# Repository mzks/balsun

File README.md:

# balsun - Balloon adaptive link board with Wi-SUN

This is an arduino-compatible board for balloon experiments.

## Features

 - Arduino UNO R4 Minima-compatible hardware
 - Low EMC noise for general balloon RF system
 - Wi-SUN FAN communication (MIC/TELEC, FCC)
 - Open hardware and software

## Specifications

 - MCU Renesas RA4M1
 - 5V IOs (GPIO, UART, SCI, I2C, CAN, ADC, DAC, OpAmp) with castellated holes
 - Write bootloader/sketch/program via USB type-C
 - Multi power sources (1.5--5V) and more (users can mount their regurator via through holes)
 - PCB size is 64.5 * 53.4 mm, FR-4 1.6 mm
 - Wi-SUN with BP35C5 (RoHM) and two types of the anntena

## How can I get?

All hardware design is published as KiCAD files.
You can ask some manifactures to build them.
If you are customer of JLCPCB, Elecrow, FusionPCB, or PCBWay, you can find the zip files including everything to build PCB in [here](/hardware/info/gerber_to_order).
For PCBA, BOM and Pos files are [here](/hardware/info).
All parts are available in Mouser (2024 Oct. 24).

## Contact
Keita Mizukoshi (mizukoshi.keita@jaxa.jp)

## Local information
Japanese specific information and discussion among local balloon community in [jp-docs](/docs/jp-docs.md).

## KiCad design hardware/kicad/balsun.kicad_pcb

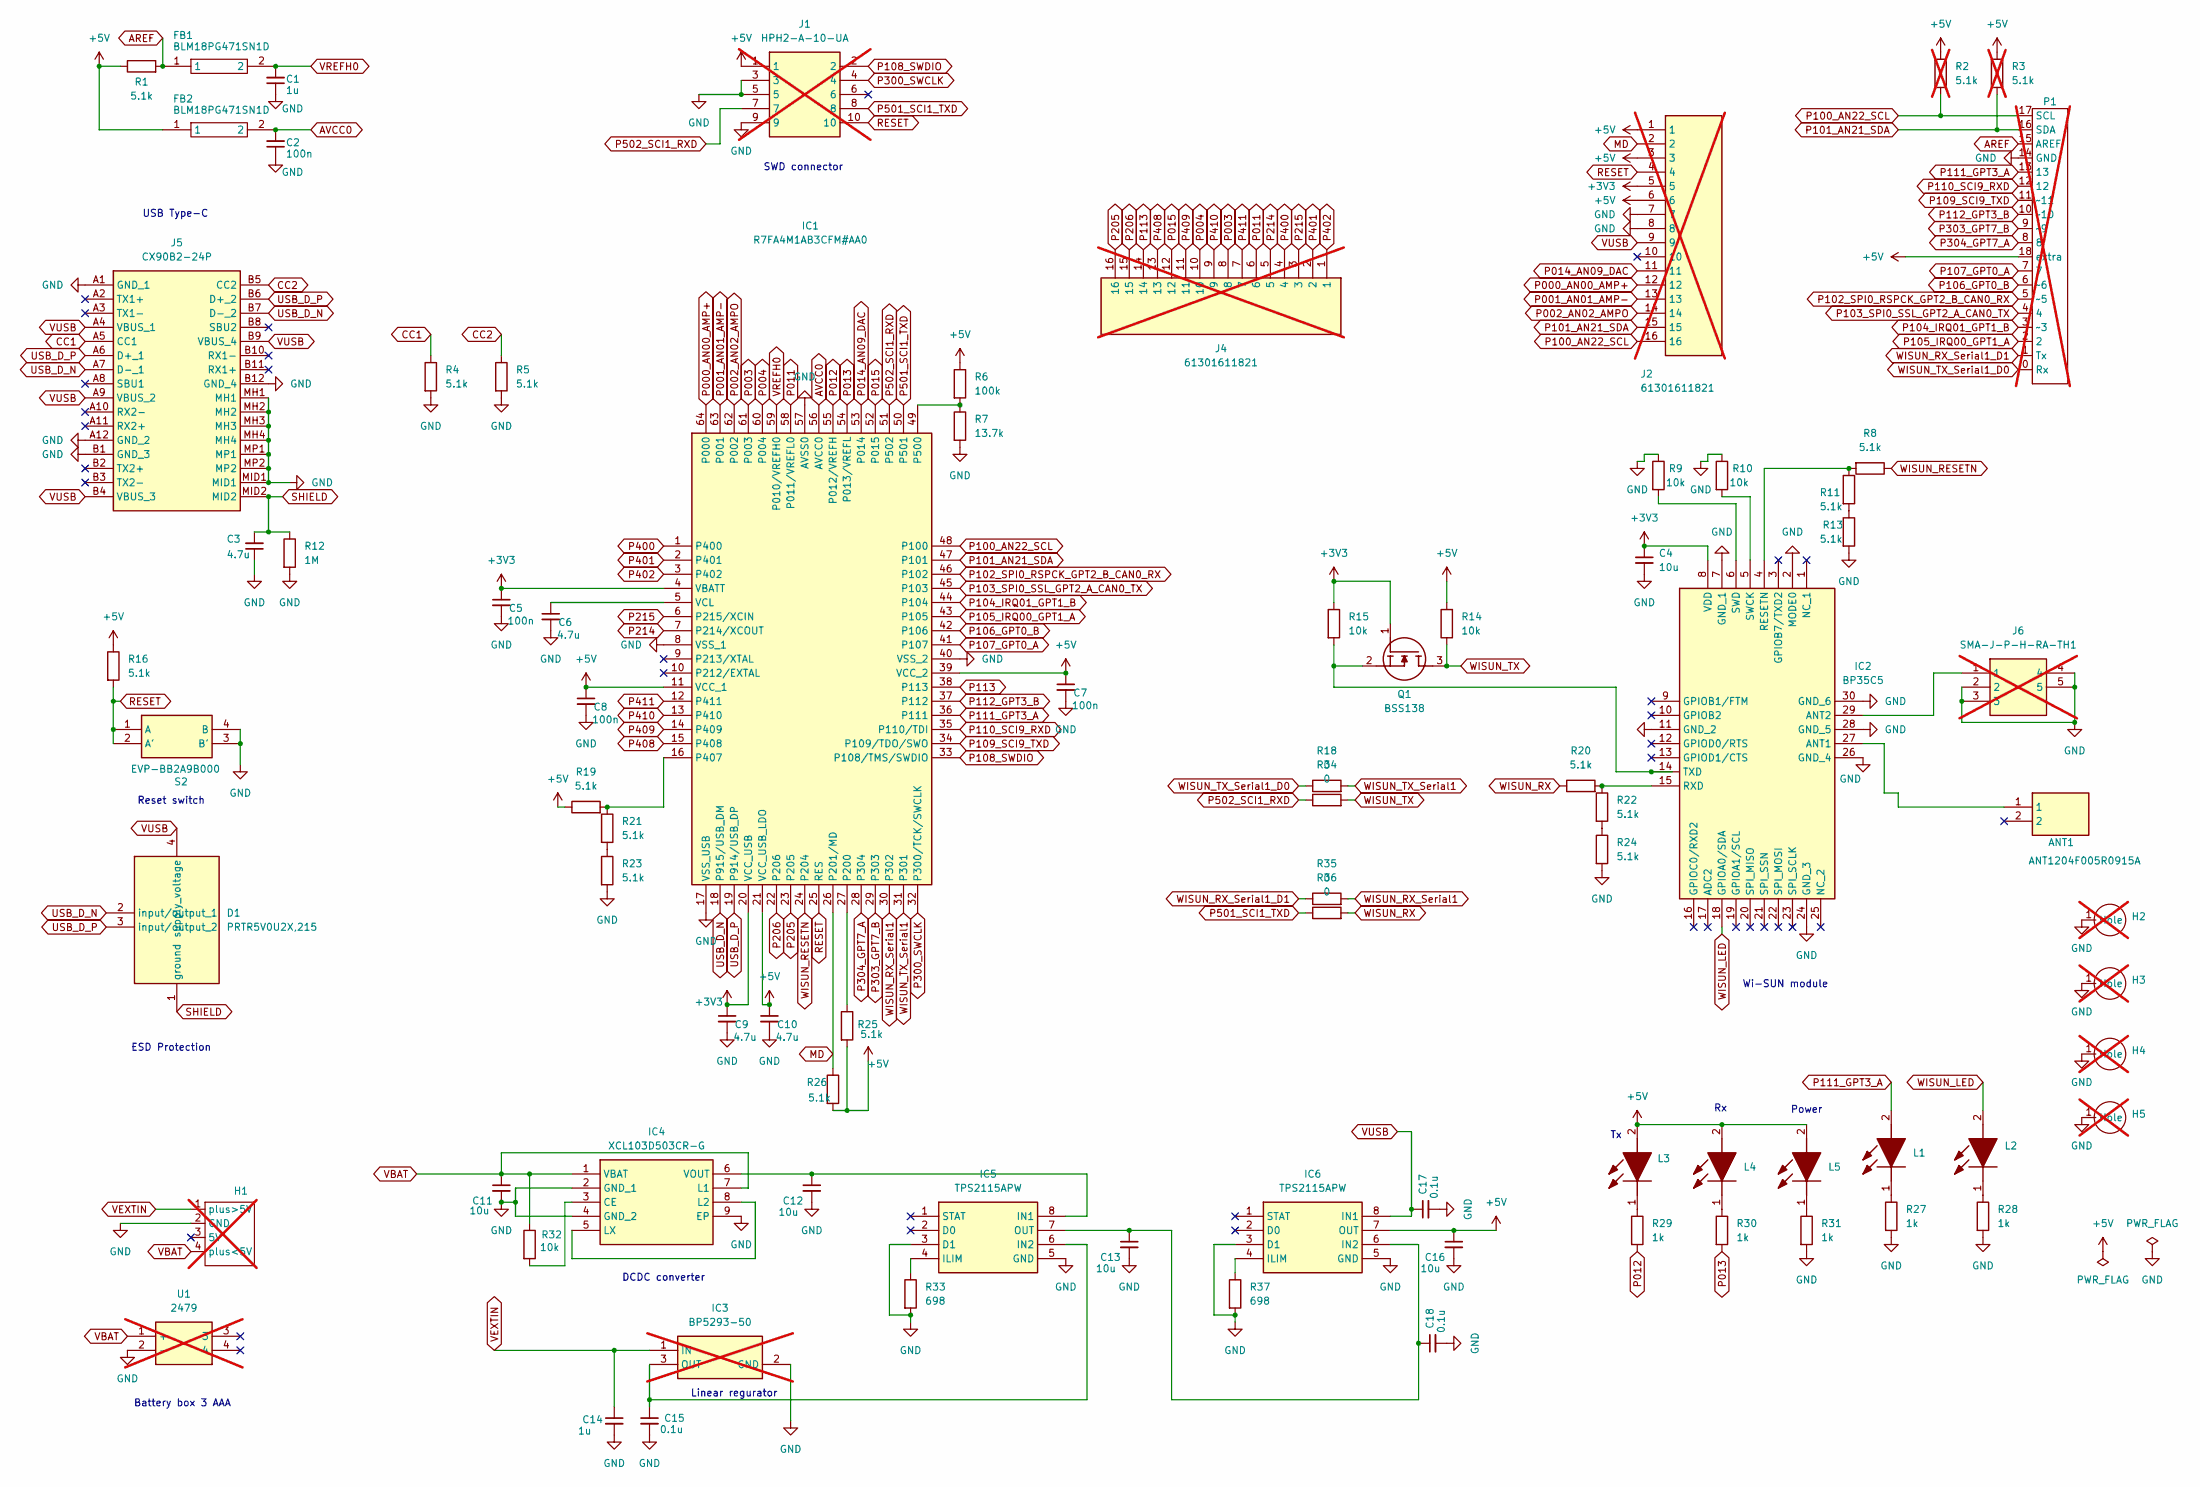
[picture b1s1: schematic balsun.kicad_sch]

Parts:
ANT1: ANT1204F005R0915A; Manufacturer_Part_Number ANT1204F005R0915A; Mouser Part Number 603-ANT1204F005R0915
C1, C14: 1u; C_0603_1608Metric; Mouser Part Number 603-CC603KRX5R6BB105
C2, C5, C7, C8: 100n; C_0603_1608Metric; Mouser Part Number 603-CC603KRX7R6BB104
C3, C6, C9, C10: 4.7u; C_0603_1608Metric; Mouser Part Number 603-CC603ZRY5V6BB475
C4, C11, C12, C13, C16: 10u; C_0603_1608Metric; Mouser Part Number 603-CC603MRX6S6BB106
C15, C17, C18: 0.1u; C_0603_1608Metric; Mouser Part Number 603-CC603KRX7R6BB104
D1: PRTR5V0U2X,215; PRTR5V0U2X; Manufacturer_Part_Number PRTR5V0U2X,215; Mouser Part Number 771-PRTR5V0U2X-T/R
FB1, FB2: BLM18PG471SN1D; BLM18SP221SN1B; Manufacturer_Part_Number BLM18PG471SN1D; Mouser Part Number 81-BLM18PG471SN1D
H1: power_holes; not fitted
H2, H3, H4, H5: MountingHole_3.2mm_M3; not fitted
IC1: R7FA4M1AB3CFM#AA0; QFP50P1200X1200X170-64N; Manufacturer_Part_Number R7FA4M1AB3CFM#AA0; Mouser Part Number 968-7FA4M1AB3CFM#AA0
IC2: BP35C5; Manufacturer_Part_Number BP35C5; Mouser Part Number 755-BP35C5
IC3: BP5293-50; not fitted
IC4: XCL103D503CR-G; XCL103D503CRG; Manufacturer_Part_Number XCL103D503CR-G; Mouser Part Number 865-XCL103D503CR-G
IC5, IC6: TPS2115APW; SOP65P640X120-8N; Manufacturer_Part_Number TPS2115APW; Mouser Part Number 595-TPS2115APW
J1: HPH2-A-10-UA; HDRV10W45P127_2X5_635X345X400P; Manufacturer_Part_Number HPH2-A-10-UA; Mouser Part Number 737-HPH2-A-10-UA; not fitted
J2: 61301611821; arduino_pins_2; Manufacturer_Part_Number 61301611821; Mouser Part Number 710-61301611821; not fitted
J4: 61301611821; HDRV16; Manufacturer_Part_Number 61301611821; Mouser Part Number 710-61301611821; not fitted
J5: CX90B2-24P; CX90B224P; Manufacturer_Part_Number CX90B2-24P; Mouser Part Number 798-CX90B2-24P
J6: SMA-J-P-H-RA-TH1; CON-SMA-EDGE-S; Manufacturer_Part_Number SMA-J-P-H-RA-TH1; Mouser Part Number 710-63012202124505; not fitted
L1, L2, L5: SML-P11UTT86; CSL1901MW1; Manufacturer_Part_Number SML-P11UTT86; Mouser Part Number 755-755-SML-P11UTT86
L3: SML-P11UTT86; CSL1901YW1; Manufacturer_Part_Number SML-P11UTT86; Mouser Part Number 755-755-SML-P11UTT86
L4: SML-P11UTT86; CSL1901UW1; Manufacturer_Part_Number SML-P11UTT86; Mouser Part Number 755-755-SML-P11UTT86
P1: arduino_pins1; not fitted
Q1: BSS138; SOT95P240X120-3N; Manufacturer_Part_Number BSS138; Mouser Part Number 512-BSS138
R1, R4, R5, R8, R11, R13, R16, R19, R20, R21, R22, R23, R24, R25, R26: 5.1k; R_0603_1608Metric; Mouser Part Number 667-ERA-3ARB512V
R2, R3: 5.1k; R_0603_1608Metric; Mouser Part Number 667-ERA-3ARB512V; not fitted
R6: 100k; R_0603_1608Metric; Mouser Part Number 667-ERA-3AEB104V
R7: 13.7k; R_0603_1608Metric; Mouser Part Number 667-ERA-3AEB1372V
R9, R10, R32: 10k; R_0603_1608Metric; Mouser Part Number 667-ERA-3ARB103V
R12: 1M; R_0603_1608Metric; Mouser Part Number 667-ERJ-3EKF1004V
R14, R15: 10k; R_0603_1608Metric; Mouser Part Number 667-ERA-3ARB512V
R18, R34, R35, R36: 0; R_0603_1608Metric; Mouser Part Number 667-ERJ-3GEY0R00V
R27, R28, R29, R30, R31: 1k; R_0603_1608Metric; Mouser Part Number 667-ERJ-U03J331V
R33, R37: 698; R_0603_1608Metric; Mouser Part Number 667-ERA-3AEB6980V
S2: EVP-BB2A9B000; EVPBB2A9B000; Manufacturer_Part_Number EVP-BB2A9B000; Mouser Part Number 667-EVP-BB2A9B000
U1: 2479; Manufacturer_Part_Number 2479; Mouser Part Number 534-2479; not fitted

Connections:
+3V3: C4.1, C5.1, C9.1, IC1.4 (VBATT), IC1.20 (VCC_USB), IC2.8 (VDD), J2.5, Q1.1 (G), R15.1
+5V: C7.1, C8.1, C10.1, C16.1, FB2.1, IC1.11 (VCC_1), IC1.21 (VCC_USB_LDO), IC1.39 (VCC_2), IC6.7 (OUT), J1.1, J2.1, J2.3, J2.6, L3.2 (A), L4.2 (A), L5.2 (A), P1.18 (extra), R1.1, R2.1, R3.1, R6.1, R14.2, R16.1, R19.1, R25.2, R26.2
AREF: FB1.1, P1.15 (AREF), R1.2
AVCC0: C2.2, FB2.2, IC1.56 (AVCC0)
CC1: J5.A5 (CC1), R4.1
CC2: J5.B5 (CC2), R5.1
GND: C1.1, C2.1, C3.1, C4.2, C5.2, C6.2, C7.2, C8.2, C9.2, C10.2, C11.2, C12.2, C13.2, C14.2, C15.2, C16.2, C17.2, C18.2, H1.2 (GND), H2.1 (Hole), H3.1 (Hole), H4.1 (Hole), H5.1 (Hole), IC1.8 (VSS_1), IC1.17 (VSS_USB), IC1.40 (VSS_2), IC1.57 (AVSS0), IC2.2 (MODE0), IC2.7 (GND_1), IC2.11 (GND_2), IC2.24 (GND_3), IC2.26 (GND_4), IC2.28 (GND_5), IC2.30 (GND_6), IC3.2 (GND), IC4.2 (GND_1), IC4.4 (GND_2), IC4.9 (EP), IC5.3 (D1), IC5.5 (GND), IC6.3 (D1), IC6.5 (GND), J1.3, J1.5, J1.9, J2.7, J2.8, J5.A1 (GND_1), J5.A12 (GND_2), J5.B1 (GND_3), J5.B12 (GND_4), J5.MH1, J5.MH2, J5.MH3, J5.MH4, J5.MID1, J5.MP1, J5.MP2, J6.2, J6.3, J6.4, J6.5, P1.14 (GND), R4.2, R5.2, R7.2, R9.1, R10.1, R12.2, R13.2, R23.2, R24.2, R27.2, R28.2, R31.2, R33.2, R37.2, S2.3 (B'), S2.4 (B), U1.2 (-)
MD: IC1.26 (P201/MD), J2.2, R26.1
unnamed: IC1.27 (P200), R25.1
unnamed: IC1.16 (P407), R19.2, R21.1
unnamed: IC1.49 (P500), R6.2, R7.1
unnamed: C6.1, IC1.5 (VCL)
unnamed: ANT1.1, IC2.27 (ANT1)
unnamed: IC2.29 (ANT2), J6.1
unnamed: IC2.4 (RESETN), R8.2, R11.1
unnamed: IC2.15 (RXD), R20.2, R22.1
unnamed: IC2.5 (SWCK), R10.2
unnamed: IC2.6 (SWD), R9.2
unnamed: IC2.14 (TXD), Q1.2 (S), R15.2
unnamed: C15.1, IC3.3 (OUT), IC5.6 (IN2)
unnamed: IC4.3 (CE), R32.2
unnamed: IC4.5 (LX), IC4.8 (L2)
unnamed: C12.1, IC4.6 (VOUT), IC5.8 (IN1)
unnamed: IC5.4 (ILIM), R33.1
unnamed: C13.1, C18.1, IC5.7 (OUT), IC6.6 (IN2)
unnamed: IC6.4 (ILIM), R37.1
unnamed: L1.1 (K), R27.1
unnamed: L2.1 (K), R28.1
unnamed: L3.1 (K), R29.1
unnamed: L4.1 (K), R30.1
unnamed: L5.1 (K), R31.1
unnamed: R11.2, R13.1
unnamed: R21.2, R23.1
unnamed: R22.2, R24.1
P000_AN00_AMP+: IC1.64 (P000), J2.12
P001_AN01_AMP-: IC1.63 (P001), J2.13
P002_AN02_AMPO: IC1.62 (P002), J2.14
P003: IC1.61 (P003), J4.8
P004: IC1.60 (P004), J4.10
P011: IC1.58 (P011/VREFL0), J4.6
P012: IC1.55 (P012/VREFH), R29.2
P013: IC1.54 (P013/VREFL), R30.2
P014_AN09_DAC: IC1.53 (P014), J2.11
P015: IC1.52 (P015), J4.12
P100_AN22_SCL: IC1.48 (P100), J2.16, P1.17 (SCL), R2.2
P101_AN21_SDA: IC1.47 (P101), J2.15, P1.16 (SDA), R3.2
P102_SPI0_RSPCK_GPT2_B_CAN0_RX: IC1.46 (P102), P1.5 (~5)
P103_SPI0_SSL_GPT2_A_CAN0_TX: IC1.45 (P103), P1.4
P104_IRQ01_GPT1_B: IC1.44 (P104), P1.3 (~3)
P105_IRQ00_GPT1_A: IC1.43 (P105), P1.2
P106_GPT0_B: IC1.42 (P106), P1.6 (~6)
P107_GPT0_A: IC1.41 (P107), P1.7
P108_SWDIO: IC1.33 (P108/TMS/SWDIO), J1.2
P109_SCI9_TXD: IC1.34 (P109/TDO/SWO), P1.11 (~11)
P110_SCI9_RXD: IC1.35 (P110/TDI), P1.12
P111_GPT3_A: IC1.36 (P111), L1.2 (A), P1.13
P112_GPT3_B: IC1.37 (P112), P1.10 (~10)
P113: IC1.38 (P113), J4.14
P205: IC1.23 (P205), J4.16
P206: IC1.22 (P206), J4.15
P214: IC1.7 (P214/XCOUT), J4.5
P215: IC1.6 (P215/XCIN), J4.3
P300_SWCLK: IC1.32 (P300/TCK/SWCLK), J1.4
P303_GPT7_B: IC1.29 (P303), P1.9 (~9)
P304_GPT7_A: IC1.28 (P304), P1.8
P400: IC1.1 (P400), J4.4
P401: IC1.2 (P401), J4.2
P402: IC1.3 (P402), J4.1
P408: IC1.15 (P408), J4.13
P409: IC1.14 (P409), J4.11
P410: IC1.13 (P410), J4.9
P411: IC1.12 (P411), J4.7
P501_SCI1_TXD: IC1.50 (P501), J1.8, R36.1
P502_SCI1_RXD: IC1.51 (P502), J1.7, R34.1
RESET: IC1.25 (RES), J1.10, J2.4, R16.2, S2.1 (A), S2.2 (A')
SHIELD: C3.2, D1.1 (ground), J5.MID2, R12.1
USB_D_N: D1.2 (input/output_1), IC1.18 (P915/USB_DM), J5.A7 (D-_1), J5.B7 (D-_2)
USB_D_P: D1.3 (input/output_2), IC1.19 (P914/USB_DP), J5.A6 (D+_1), J5.B6 (D+_2)
VBAT: C11.1, H1.4 (plus<5V), IC4.1 (VBAT), IC4.7 (L1), R32.1, U1.1 (+)
VEXTIN: C14.1, H1.1 (plus>5V), IC3.1 (IN)
VREFH0: C1.2, FB1.2, IC1.59 (P010/VREFH0)
VUSB: C17.1, D1.4 (supply_voltage), IC6.8 (IN1), J2.9, J5.A4 (VBUS_1), J5.A9 (VBUS_2), J5.B4 (VBUS_3), J5.B9 (VBUS_4)
WISUN_LED: IC2.18 (GPIOA0/SDA), L2.2 (A)
WISUN_RESETN: IC1.24 (P204), R8.1
WISUN_RX: R20.1, R36.2
WISUN_RX_Serial1: IC1.30 (P302), R35.2
WISUN_RX_Serial1_D1: P1.1 (Tx), R35.1
WISUN_TX: Q1.3 (D), R14.1, R34.2
WISUN_TX_Serial1: IC1.31 (P301), R18.2
WISUN_TX_Serial1_D0: P1.0 (Rx), R18.1

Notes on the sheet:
Reset switch
USB Type-C
Power
SWD connector
Wi-SUN module
ESD Protection
DCDC converter
Linear regurator
Battery box 3 AAA

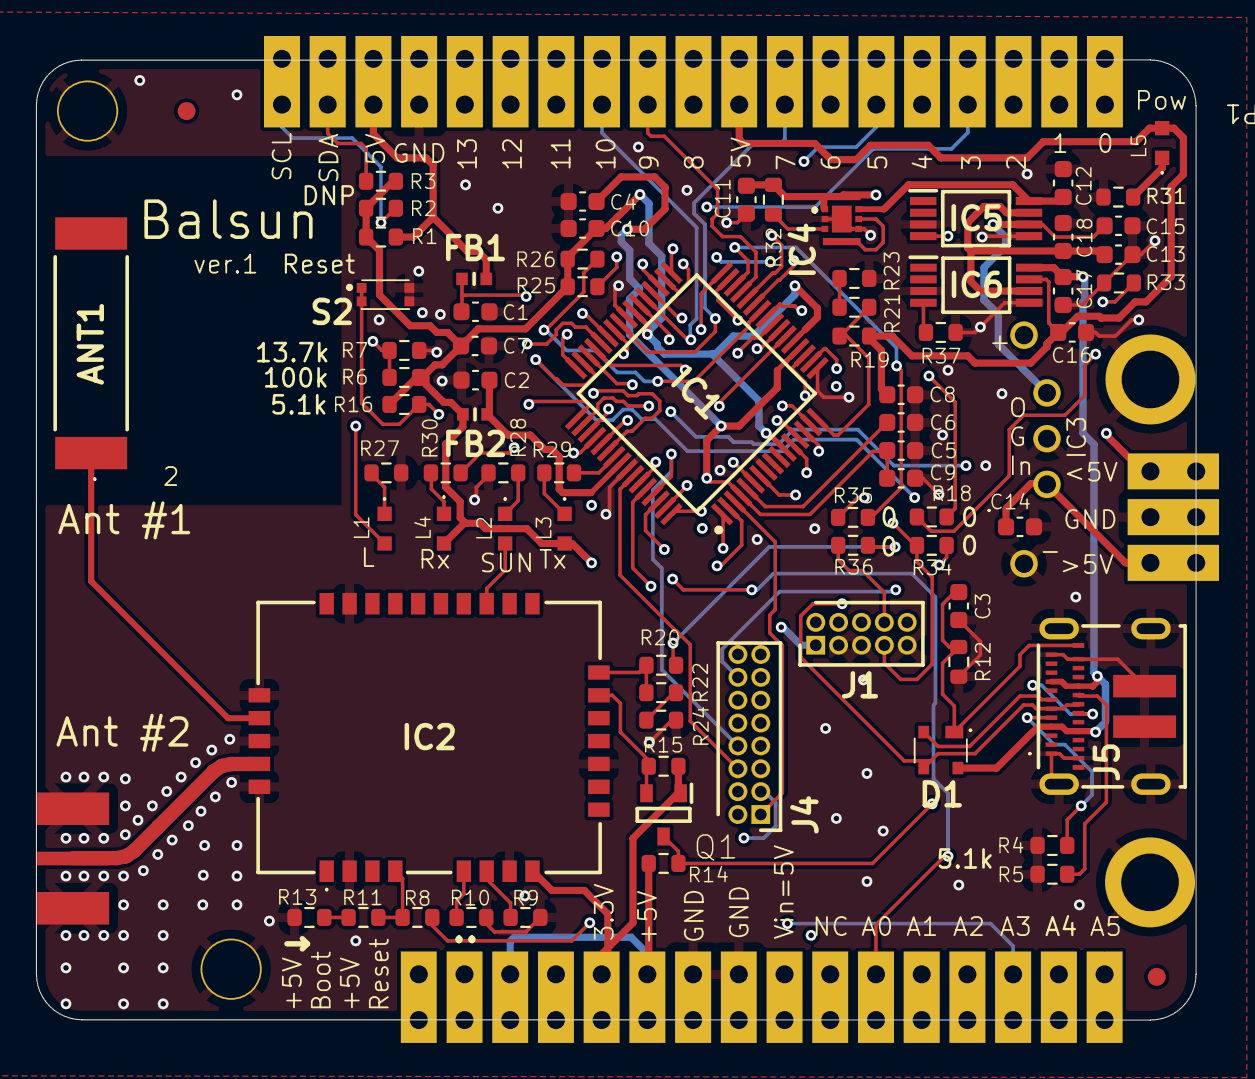
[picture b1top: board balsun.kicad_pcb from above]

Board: 4 copper layers, 64.4 x 53.3 mm, 83 parts (1 on the bottom side), 90 nets.

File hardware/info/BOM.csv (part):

"Reference","Value","Datasheet","Footprint","Qty","DNP","Manufacturer_Name","Mouser Part Number","Mouser Price/Stock"
"ANT1","ANT1204F005R0915A","https://eu.mouser.com/datasheet/2/447/datasheet_pulse_915mhz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","ANT1204F005R0915A","1","","Pulse Electronics","603-ANT1204F005R0915","https://www.mouser.co.uk/ProductDetail/PulseLarsen-Antennas/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"
"C1","1u","~","Capacitor_SMD:C_0603_1608Metric","1","","","603-CC603KRX5R6BB105",""
"C2","100n","~","Capacitor_SMD:C_0603_1608Metric","1","","","603-CC603KRX7R6BB104",""
"C3","4.7u","~","Capacitor_SMD:C_0603_1608Metric","1","","","603-CC603ZRY5V6BB475",""
"C4","10u","~","Capacitor_SMD:C_0603_1608Metric","1","","","603-CC603MRX6S6BB106",""
"C5","100n","~","Capacitor_SMD:C_0603_1608Metric","1","","","603-CC603KRX7R6BB104",""
"C6","4.7u","~","Capacitor_SMD:C_0603_1608Metric","1","","","603-CC603ZRY5V6BB475",""
"C7","100n","~","Capacitor_SMD:C_0603_1608Metric","1","","","603-CC603KRX7R6BB104",""
"C8","100n","~","Capacitor_SMD:C_0603_1608Metric","1","","","603-CC603KRX7R6BB104",""
"C9","4.7u","~","Capacitor_SMD:C_0603_1608Metric","1","","","603-CC603ZRY5V6BB475",""
"C10","4.7u","~","Capacitor_SMD:C_0603_1608Metric","1","","","603-CC603ZRY5V6BB475",""
"C11","10u","~","Capacitor_SMD:C_0603_1608Metric","1","","","603-CC603MRX6S6BB106",""
"C12","10u","~","Capacitor_SMD:C_0603_1608Metric","1","","","603-CC603MRX6S6BB106",""
"C13","10u","~","Capacitor_SMD:C_0603_1608Metric","1","","","603-CC603MRX6S6BB106",""
"C14","1u","~","Capacitor_SMD:C_0603_1608Metric","1","","","603-CC603KRX5R6BB105",""
"C15","0.1u","~","Capacitor_SMD:C_0603_1608Metric","1","","","603-CC603KRX7R6BB104",""
"C16","10u","~","Capacitor_SMD:C_0603_1608Metric","1","","","603-CC603MRX6S6BB106",""
"C17","0.1u","~","Capacitor_SMD:C_0603_1608Metric","1","","","603-CC603KRX7R6BB104",""
"C18","0.1u","~","Capacitor_SMD:C_0603_1608Metric","1","","","603-CC603KRX7R6BB104",""
"D1","PRTR5V0U2X,215","https://assets.nexperia.com/documents/data-sheet/PRTR5V0U2X.pdf","PRTR5V0U2X","1","","Nexperia","771-PRTR5V0U2X-T/R","https://www.mouser.co.uk/ProductDetail/Nexperia/PRTR5V0U2X21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"
"FB1","BLM18PG471SN1D","http://www.murata.com/~/media/webrenewal/support/library/cat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","BLM18SP221SN1B","1","","Murata Electronics","81-BLM18PG471SN1D","https://www.mouser.co.uk/ProductDetail/Murata-Electronics/BL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"
"FB2","BLM18PG471SN1D","http://www.murata.com/~/media/webrenewal/support/library/cat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","BLM18SP221SN1B","1","","Murata Electronics","81-BLM18PG471SN1D","https://www.mouser.co.uk/ProductDetail/Murata-Electronics/BL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"
"H1","~","","Library:power_holes","1","DNP","","",""
"H2","~","","SamacSys_Parts:MountingHole_3.2mm_M3","1","DNP","","",""
"H3","~","","SamacSys_Parts:MountingHole_3.2mm_M3","1","DNP","","",""
"H4","~","","SamacSys_Parts:MountingHole_3.2mm_M3","1","DNP","","",""
"H5","~","","SamacSys_Parts:MountingHole_3.2mm_M3","1","DNP","","",""
"IC1","R7FA4M1AB3CFM#AA0","https://www.renesas.com/document/dst/renesas-ra4m1-group-dat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","QFP50P1200X1200X170-64N","1","","Renesas Electronics","968-7FA4M1AB3CFM#AA0","https://www.mouser.co.uk/ProductDetail/Renesas-Electronics/R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"
"IC2","BP35C5","https://fscdn.rohm.com/en/products/databook/datasheet/module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","BP35C5","1","","ROHM Semiconductor","755-BP35C5",""
"IC3","BP5293-50","https://componentsearchengine.com/Datasheets/2/MC7805BDTRKG.pdf","SamacSys_Parts:BP5293-50","1","DNP","","","https://www.mouser.co.uk/ProductDetail/onsemi/MC7805BDTRKG?q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"
"IC4","XCL103D503CR-G","https://www.torexsemi.com/file/xcl102/XCL102-103.pdf","XCL103D503CRG","1","","Torex","865-XCL103D503CR-G","https://www.mouser.co.uk/ProductDetail/Torex-Semiconductor/X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"
"IC5","TPS2115APW","http://www.ti.com/lit/ds/symlink/tps2115a.pdf","SOP65P640X120-8N","1","","Texas Instruments","595-TPS2115APW","https://www.mouser.co.uk/ProductDetail/Texas-Instruments/TPS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"
"IC6","TPS2115APW","http://www.ti.com/lit/ds/symlink/tps2115a.pdf","SOP65P640X120-8N","1","","Texas Instruments","595-TPS2115APW","https://www.mouser.co.uk/ProductDetail/Texas-Instruments/TPS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"
"J1","HPH2-A-10-UA","","HDRV10W45P127_2X5_635X345X400P","1","DNP","Adam Tech","737-HPH2-A-10-UA",""
"J2","61301611821","https://www.we-online.com/catalog/datasheet/61301611821.pdf","SamacSys_Parts:arduino_pins_2","1","DNP","Wurth Elektronik","710-61301611821","https://www.mouser.co.uk/ProductDetail/Wurth-Elektronik/6130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"
"J4","61301611821","https://www.we-online.com/catalog/datasheet/61301611821.pdf","SamacSys_Parts:HDRV16","1","DNP","Wurth Elektronik","710-61301611821","https://www.mouser.co.uk/ProductDetail/Wurth-Elektronik/6130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"
"J5","CX90B2-24P","https://www.hirose.com/en/product/document?clcode=CL0480-088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","CX90B224P","1","","Hirose","798-CX90B2-24P",""
"J6","SMA-J-P-H-RA-TH1","https://www.we-online.com/components/products/datasheet/6301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","SamacSys_Parts:CON-SMA-EDGE-S","1","DNP","SAMTEC","710-63012202124505",""
"L1","SML-P11UTT86","https://fscdn.rohm.com/en/products/databook/datasheet/opto/l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","SamacSys_Parts:CSL1901MW1","1","","ROHM Semiconductor","755-755-SML-P11UTT86","https://www.mouser.co.uk/ProductDetail/ROHM-Semiconductor/SM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"
"L2","SML-P11UTT86","https://fscdn.rohm.com/en/products/databook/datasheet/opto/l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","SamacSys_Parts:CSL1901MW1","1","","ROHM Semiconductor","755-755-SML-P11UTT86","https://www.mouser.co.uk/ProductDetail/ROHM-Semiconductor/SM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"
"L3","SML-P11UTT86","https://fscdn.rohm.com/en/products/databook/datasheet/opto/l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","SamacSys_Parts:CSL1901YW1","1","","ROHM Semiconductor","755-755-SML-P11UTT86","https://www.mouser.co.uk/ProductDetail/ROHM-Semiconductor/SM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"
"L4","SML-P11UTT86","https://fscdn.rohm.com/en/products/databook/datasheet/opto/l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","SamacSys_Parts:CSL1901UW1","1","","ROHM Semiconductor","755-755-SML-P11UTT86","https://www.mouser.co.uk/ProductDetail/ROHM-Semiconductor/SM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"
"L5","SML-P11UTT86","https://fscdn.rohm.com/en/products/databook/datasheet/opto/l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","SamacSys_Parts:CSL1901MW1","1","","ROHM Semiconductor","755-755-SML-P11UTT86","https://www.mouser.co.uk/ProductDetail/ROHM-Semiconductor/SM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"
"P1","~","","SamacSys_Parts:arduino_pins1","1","DNP","","",""
"Q1","BSS138","https://www.onsemi.com/pub/Collateral/BSS138-D.PDF","SOT95P240X120-3N","1","","onsemi","512-BSS138","https://www.mouser.co.uk/ProductDetail/onsemi-Fairchild/BSS1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"
"R1","5.1k","~","Resistor_SMD:R_0603_1608Metric","1","","","667-ERA-3ARB512V",""
"R2","5.1k","~","Resistor_SMD:R_0603_1608Metric","1","DNP","","667-ERA-3ARB512V",""
"R3","5.1k","~","Resistor_SMD:R_0603_1608Metric","1","DNP","","667-ERA-3ARB512V",""
"R4","5.1k","~","Resistor_SMD:R_0603_1608Metric","1","","","667-ERA-3ARB512V",""
"R5","5.1k","~","Resistor_SMD:R_0603_1608Metric","1","","","667-ERA-3ARB512V",""
"R6","100k","~","Resistor_SMD:R_0603_1608Metric","1","","","667-ERA-3AEB104V",""
"R7","13.7k","~","Resistor_SMD:R_0603_1608Metric","1","","","667-ERA-3AEB1372V",""
"R8","5.1k","~","Resistor_SMD:R_0603_1608Metric","1","","","667-ERA-3ARB512V",""
"R9","10k","~","Resistor_SMD:R_0603_1608Metric","1","","","667-ERA-3ARB103V",""
"R10","10k","~","Resistor_SMD:R_0603_1608Metric","1","","","667-ERA-3ARB103V",""
"R11","5.1k","~","Resistor_SMD:R_0603_1608Metric","1","","","667-ERA-3ARB512V",""
"R12","1M","~","Resistor_SMD:R_0603_1608Metric","1","","","667-ERJ-3EKF1004V",""
"R13","5.1k","~","Resistor_SMD:R_0603_1608Metric","1","","","667-ERA-3ARB512V",""
"R14","10k","~","Resistor_SMD:R_0603_1608Metric","1","","","667-ERA-3ARB512V",""
"R15","10k","~","Resistor_SMD:R_0603_1608Metric","1","","","667-ERA-3ARB512V",""
"R16","5.1k","~","Resistor_SMD:R_0603_1608Metric","1","","","667-ERA-3ARB512V",""
"R18","0","~","Resistor_SMD:R_0603_1608Metric","1","","","667-ERJ-3GEY0R00V",""
"R19","5.1k","~","Resistor_SMD:R_0603_1608Metric","1","","","667-ERA-3ARB512V",""
"R20","5.1k","~","Resistor_SMD:R_0603_1608Metric","1","","","667-ERA-3ARB512V",""
"R21","5.1k","~","Resistor_SMD:R_0603_1608Metric","1","","","667-ERA-3ARB512V",""
"R22","5.1k","~","Resistor_SMD:R_0603_1608Metric","1","","","667-ERA-3ARB512V",""
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
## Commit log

2024-10-24 remove tentative license
2024-10-24 Add CC-BY-SA LICENSE for hardware
2024-10-24 Add KiCAD files
2024-10-24 Add design information
2024-10-24 add view files
2024-10-24 add license for arduino example
2024-10-24 start to write README.md
2024-10-24 update gitignore file
2024-10-24 short explanations
2024-10-24 Add license at the top
2024-10-28 Add grouped BOMs
2024-11-01 add hardware design files descriptions
2024-11-04 update pattern
2024-11-04 add photo
2024-11-04 update photo
2025-01-15 Add tentative instruction for alpha version check
